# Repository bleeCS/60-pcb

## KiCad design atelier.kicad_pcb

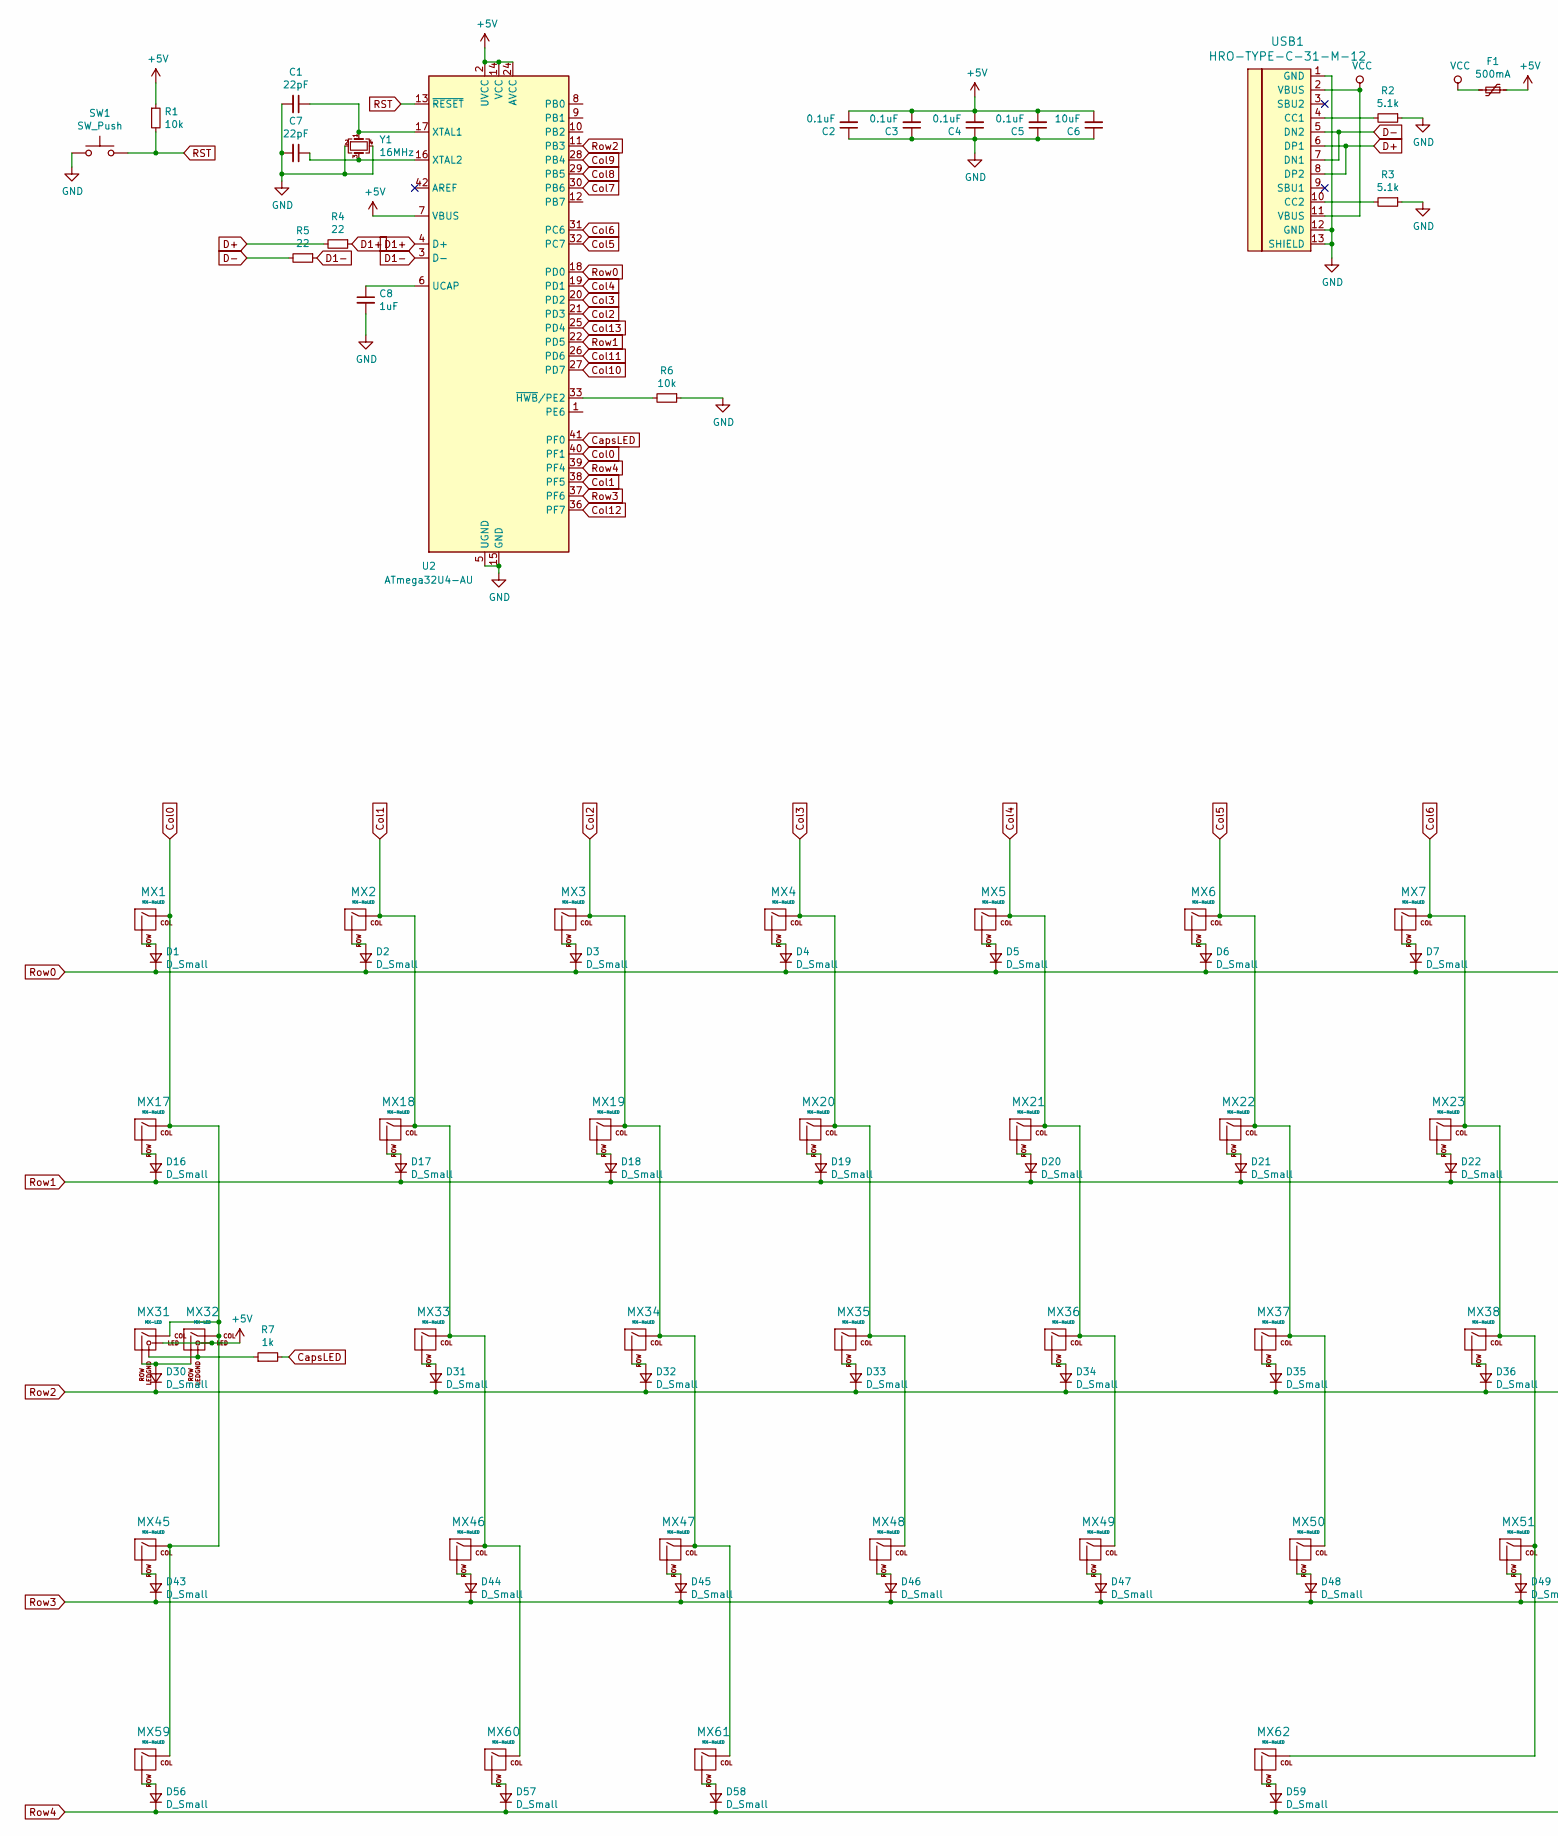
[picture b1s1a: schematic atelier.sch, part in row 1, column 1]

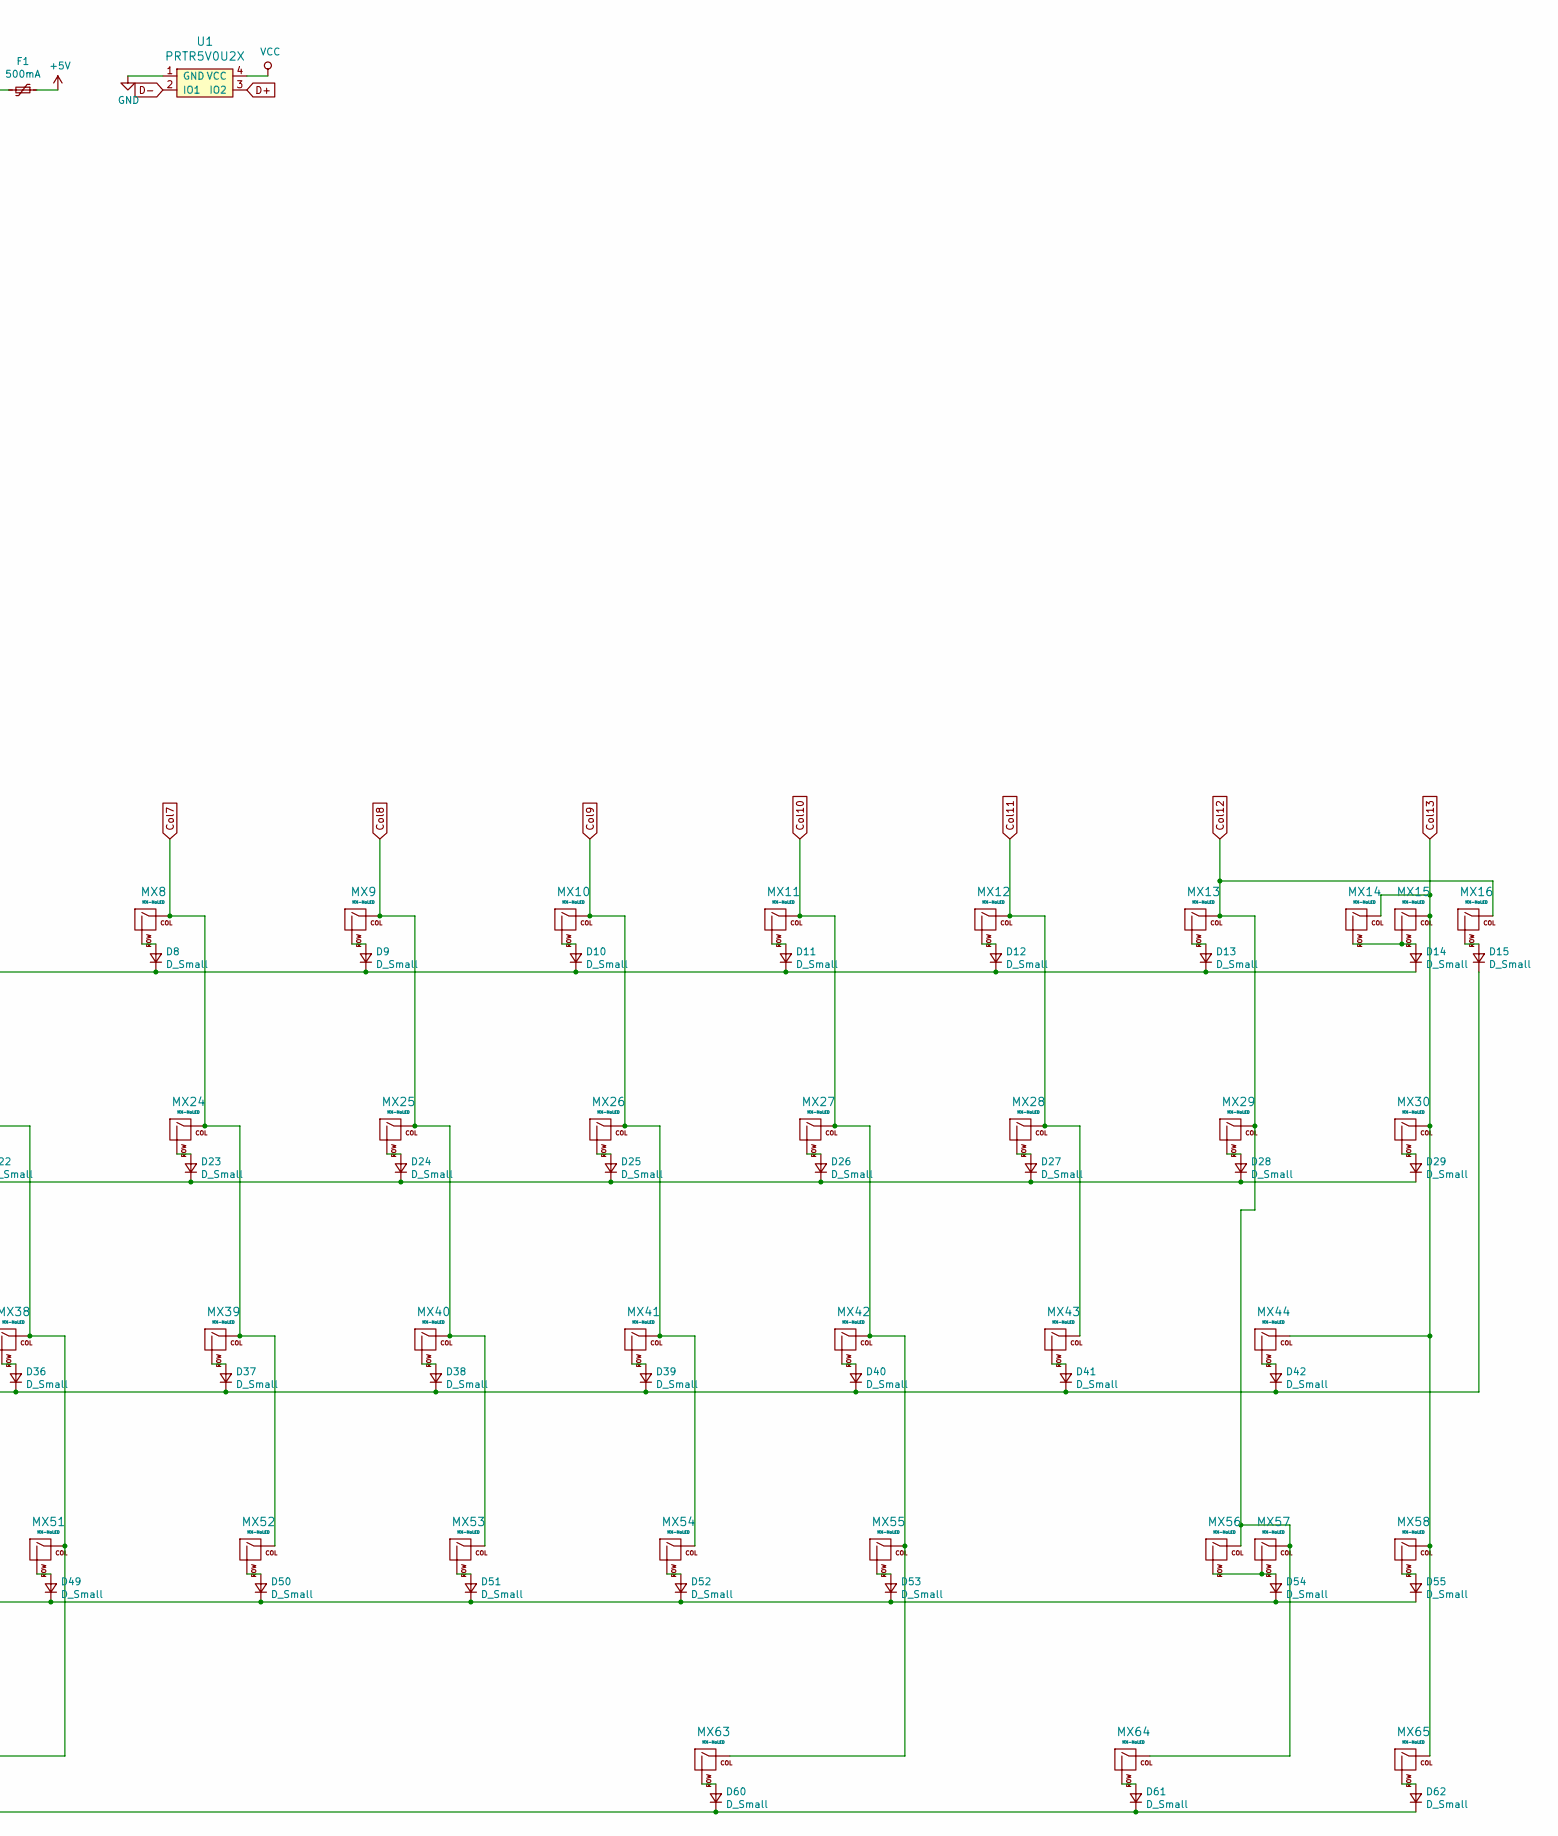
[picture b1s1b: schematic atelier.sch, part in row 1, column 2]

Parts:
C1, C7: 22pF; C_0805_2012Metric
C2, C3, C4, C5: 0.1uF; C_0805_2012Metric
C6: 10uF; C_0805_2012Metric
C8: 1uF; C_0805_2012Metric
D1, D2, D3, D4, D5, D6, D7, D8, D9, D10, D11, D12, D13, D14, D15, D16, D17, D18, D19, D20, D21, D22, D23, D24, D25, D26, D27, D28, D29, D30, D31, D32, D33, D34, D35, D36, D37, D38, D39, D40, D41, D42, D43, D44, D45, D46, D47, D48, D49, D50, D51, D52, D53, D54, D55, D56, D57, D58, D59, D60, D61, D62: D_Small; D_SOD-123
F1: 500mA; Fuse_1206_3216Metric
MX1, MX2, MX3, MX4, MX5, MX6, MX7, MX8, MX9, MX10, MX11, MX12, MX13, MX14, MX16, MX18, MX19, MX20, MX21, MX22, MX23, MX24, MX25, MX26, MX27, MX28, MX29, MX33, MX34, MX35, MX36, MX37, MX38, MX39, MX40, MX41, MX42, MX43, MX46, MX47, MX48, MX49, MX50, MX51, MX52, MX53, MX54, MX55, MX58, MX60, MX64: MX-NoLED; MXOnly-1U-NoLED
MX15: MX-NoLED; MXOnly-2U-NoLED
MX17, MX30, MX59, MX61, MX63, MX65: MX-NoLED; MXOnly-1.5U-NoLED
MX31: MX-LED; MXOnly-1.25U-FLIPPED
MX32: MX-LED; MXOnly-1.75U
MX44: MX-NoLED; MXOnly-2.25U-ReversedStabilizers-NoLED
MX45: MX-NoLED; MXOnly-2.25U-NoLED
MX56: MX-NoLED; MXOnly-1.75U-NoLED
MX57: MX-NoLED; MXOnly-2.75U-NoLED
MX62: MX-NoLED; MXOnly-7U-ReversedStabilizers-NoLED
R1, R6: 10k; R_0805_2012Metric
R2, R3: 5.1k; R_0805_2012Metric
R4, R5: 22; R_0805_2012Metric
R7: 1k; R_0805_2012Metric
SW1: SW_Push; SKQG-1155865
U1: PRTR5V0U2X; SOT143B
U2: ATmega32U4-AU; TQFP-44_10x10mm_P0.8mm
USB1: HRO-TYPE-C-31-M-12
Y1: 16MHz; Crystal_SMD_3225-4Pin_3.2x2.5mm

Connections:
+5V: C2.2, C3.2, C4.2, C5.2, C6.2, F1.1, MX31.3 (LED), MX32.3 (LED), R1.1, U2.2 (UVCC), U2.7 (VBUS), U2.14 (VCC), U2.24 (AVCC), U2.34 (VCC), U2.44 (AVCC)
CapsLED: R7.2, U2.41 (PF0)
Col0: MX1.1 (COL), MX17.1 (COL), MX31.1 (COL), MX32.1 (COL), MX45.1 (COL), MX59.1 (COL), U2.40 (PF1)
Col1: MX2.1 (COL), MX18.1 (COL), MX33.1 (COL), MX46.1 (COL), MX60.1 (COL), U2.38 (PF5)
Col2: MX3.1 (COL), MX19.1 (COL), MX34.1 (COL), MX47.1 (COL), MX61.1 (COL), U2.21 (PD3)
Col3: MX4.1 (COL), MX20.1 (COL), MX35.1 (COL), MX48.1 (COL), U2.20 (PD2)
Col4: MX5.1 (COL), MX21.1 (COL), MX36.1 (COL), MX49.1 (COL), U2.19 (PD1)
Col5: MX6.1 (COL), MX22.1 (COL), MX37.1 (COL), MX50.1 (COL), U2.32 (PC7)
Col6: MX7.1 (COL), MX23.1 (COL), MX38.1 (COL), MX51.1 (COL), MX62.1 (COL), U2.31 (PC6)
Col7: MX8.1 (COL), MX24.1 (COL), MX39.1 (COL), MX52.1 (COL), U2.30 (PB6)
Col8: MX9.1 (COL), MX25.1 (COL), MX40.1 (COL), MX53.1 (COL), U2.29 (PB5)
Col9: MX10.1 (COL), MX26.1 (COL), MX41.1 (COL), MX54.1 (COL), U2.28 (PB4)
Col10: MX11.1 (COL), MX27.1 (COL), MX42.1 (COL), MX55.1 (COL), MX63.1 (COL), U2.27 (PD7)
Col11: MX12.1 (COL), MX28.1 (COL), MX43.1 (COL), U2.26 (PD6)
Col12: MX13.1 (COL), MX16.1 (COL), MX29.1 (COL), MX56.1 (COL), MX57.1 (COL), MX64.1 (COL), U2.36 (PF7)
Col13: MX14.1 (COL), MX15.1 (COL), MX30.1 (COL), MX44.1 (COL), MX58.1 (COL), MX65.1 (COL), U2.25 (PD4)
D1+: R4.1, U2.4 (D+)
D1-: R5.1, U2.3 (D-)
D+: R4.2, U1.3 (IO2), USB1.6 (DP1), USB1.8 (DP2)
D-: R5.2, U1.2 (IO1), USB1.5 (DN2), USB1.7 (DN1)
GND: C1.2, C2.1, C3.1, C4.1, C5.1, C6.1, C7.2, C8.2, R2.1, R3.1, R6.1, SW1.1, U1.1 (GND), U2.5 (UGND), U2.15 (GND), U2.23 (GND), U2.35 (GND), U2.43 (GND), USB1.1 (GND), USB1.12 (GND), USB1.13 (SHIELD), Y1.2, Y1.4
unnamed: C1.1, U2.17 (XTAL1), Y1.1
unnamed: C7.1, U2.16 (XTAL2), Y1.3
unnamed: C8.1, U2.6 (UCAP)
unnamed: D1.2 (A), MX1.2 (ROW)
unnamed: D2.2 (A), MX2.2 (ROW)
unnamed: D3.2 (A), MX3.2 (ROW)
unnamed: D4.2 (A), MX4.2 (ROW)
unnamed: D5.2 (A), MX5.2 (ROW)
unnamed: D6.2 (A), MX6.2 (ROW)
unnamed: D7.2 (A), MX7.2 (ROW)
unnamed: D8.2 (A), MX8.2 (ROW)
unnamed: D9.2 (A), MX9.2 (ROW)
unnamed: D10.2 (A), MX10.2 (ROW)
unnamed: D11.2 (A), MX11.2 (ROW)
unnamed: D12.2 (A), MX12.2 (ROW)
unnamed: D13.2 (A), MX13.2 (ROW)
unnamed: D14.2 (A), MX14.2 (ROW), MX15.2 (ROW)
unnamed: D15.2 (A), MX16.2 (ROW)
unnamed: D16.2 (A), MX17.2 (ROW)
unnamed: D17.2 (A), MX18.2 (ROW)
unnamed: D18.2 (A), MX19.2 (ROW)
unnamed: D19.2 (A), MX20.2 (ROW)
unnamed: D20.2 (A), MX21.2 (ROW)
unnamed: D21.2 (A), MX22.2 (ROW)
unnamed: D22.2 (A), MX23.2 (ROW)
unnamed: D23.2 (A), MX24.2 (ROW)
unnamed: D24.2 (A), MX25.2 (ROW)
unnamed: D25.2 (A), MX26.2 (ROW)
unnamed: D26.2 (A), MX27.2 (ROW)
unnamed: D27.2 (A), MX28.2 (ROW)
unnamed: D28.2 (A), MX29.2 (ROW)
unnamed: D29.2 (A), MX30.2 (ROW)
unnamed: D30.2 (A), MX31.2 (ROW), MX32.2 (ROW)
unnamed: D31.2 (A), MX33.2 (ROW)
unnamed: D32.2 (A), MX34.2 (ROW)
unnamed: D33.2 (A), MX35.2 (ROW)
unnamed: D34.2 (A), MX36.2 (ROW)
unnamed: D35.2 (A), MX37.2 (ROW)
unnamed: D36.2 (A), MX38.2 (ROW)
unnamed: D37.2 (A), MX39.2 (ROW)
unnamed: D38.2 (A), MX40.2 (ROW)
unnamed: D39.2 (A), MX41.2 (ROW)
unnamed: D40.2 (A), MX42.2 (ROW)
unnamed: D41.2 (A), MX43.2 (ROW)
unnamed: D42.2 (A), MX44.2 (ROW)
unnamed: D43.2 (A), MX45.2 (ROW)
unnamed: D44.2 (A), MX46.2 (ROW)
unnamed: D45.2 (A), MX47.2 (ROW)
unnamed: D46.2 (A), MX48.2 (ROW)
unnamed: D47.2 (A), MX49.2 (ROW)
unnamed: D48.2 (A), MX50.2 (ROW)
unnamed: D49.2 (A), MX51.2 (ROW)
unnamed: D50.2 (A), MX52.2 (ROW)
unnamed: D51.2 (A), MX53.2 (ROW)
unnamed: D52.2 (A), MX54.2 (ROW)
unnamed: D53.2 (A), MX55.2 (ROW)
unnamed: D54.2 (A), MX56.2 (ROW), MX57.2 (ROW)
unnamed: D55.2 (A), MX58.2 (ROW)
unnamed: D56.2 (A), MX59.2 (ROW)
unnamed: D57.2 (A), MX60.2 (ROW)
unnamed: D58.2 (A), MX61.2 (ROW)
unnamed: D59.2 (A), MX62.2 (ROW)
unnamed: D60.2 (A), MX63.2 (ROW)
unnamed: D61.2 (A), MX64.2 (ROW)
unnamed: D62.2 (A), MX65.2 (ROW)
unnamed: MX31.4 (LEDGND), MX32.4 (LEDGND), R7.1
unnamed: R2.2, USB1.4 (CC1)
unnamed: R3.2, USB1.10 (CC2)
unnamed: R6.2, U2.33 (~HWB~/PE2)
RST: R1.2, SW1.2, U2.13 (~RESET)
Row0: D1.1 (K), D2.1 (K), D3.1 (K), D4.1 (K), D5.1 (K), D6.1 (K), D7.1 (K), D8.1 (K), D9.1 (K), D10.1 (K), D11.1 (K), D12.1 (K), D13.1 (K), D14.1 (K), U2.18 (PD0)
Row1: D16.1 (K), D17.1 (K), D18.1 (K), D19.1 (K), D20.1 (K), D21.1 (K), D22.1 (K), D23.1 (K), D24.1 (K), D25.1 (K), D26.1 (K), D27.1 (K), D28.1 (K), D29.1 (K), U2.22 (PD5)
Row2: D15.1 (K), D30.1 (K), D31.1 (K), D32.1 (K), D33.1 (K), D34.1 (K), D35.1 (K), D36.1 (K), D37.1 (K), D38.1 (K), D39.1 (K), D40.1 (K), D41.1 (K), D42.1 (K), U2.11 (PB3)
Row3: D43.1 (K), D44.1 (K), D45.1 (K), D46.1 (K), D47.1 (K), D48.1 (K), D49.1 (K), D50.1 (K), D51.1 (K), D52.1 (K), D53.1 (K), D54.1 (K), D55.1 (K), U2.37 (PF6)
Row4: D56.1 (K), D57.1 (K), D58.1 (K), D59.1 (K), D60.1 (K), D61.1 (K), D62.1 (K), U2.39 (PF4)
VCC: F1.2, U1.4 (VCC), USB1.2 (VBUS), USB1.11 (VBUS)

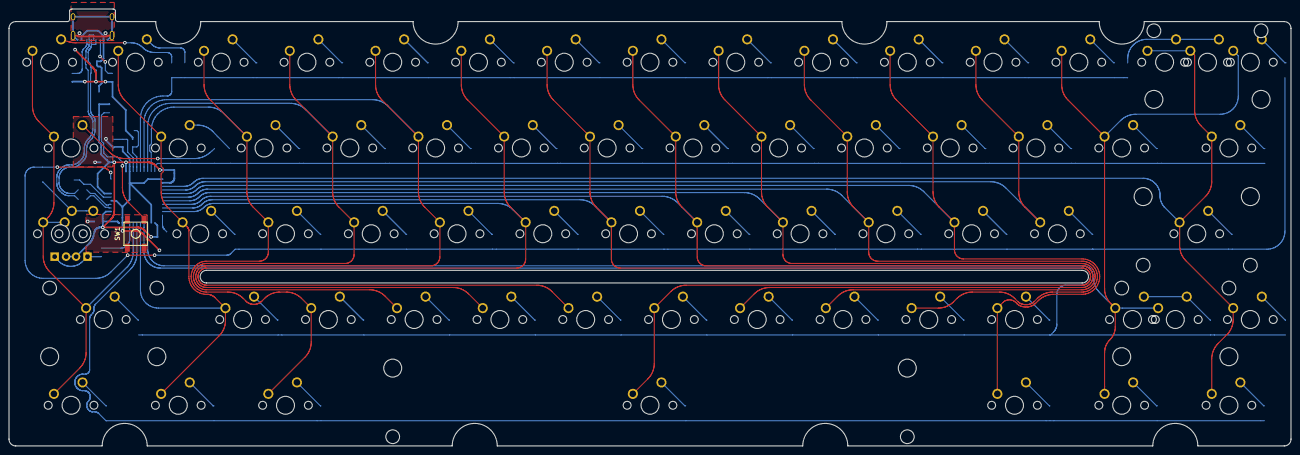
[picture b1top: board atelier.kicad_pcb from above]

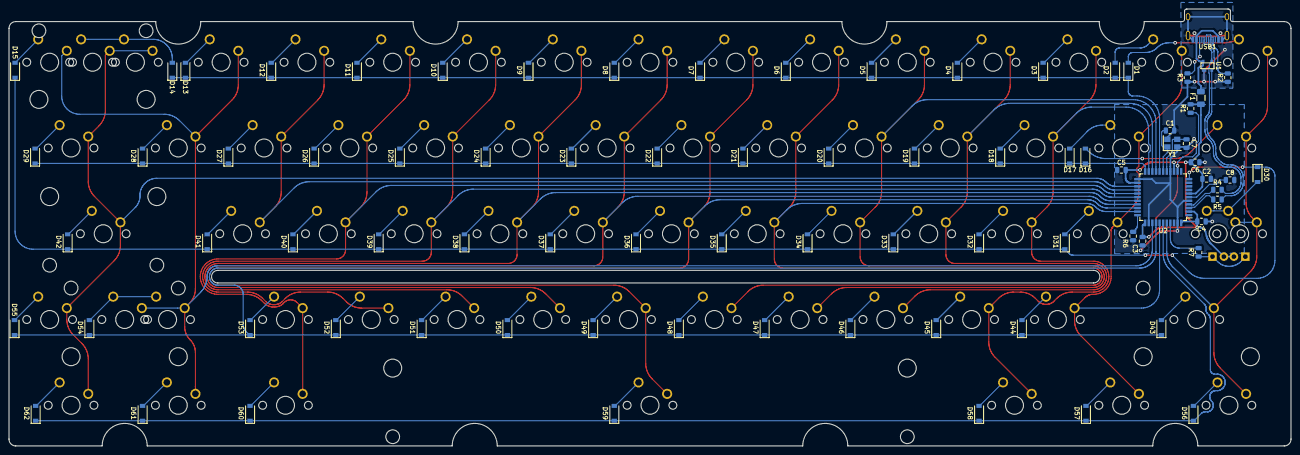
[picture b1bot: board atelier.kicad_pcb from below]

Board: 2 copper layers, 284.8 x 97.0 mm, 148 parts (82 on the bottom side), 97 nets.

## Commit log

2020-10-22 lots of changes
2020-10-22 fixes
